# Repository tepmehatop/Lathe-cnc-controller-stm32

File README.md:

# Электронная гитара токарного станка на STM32

Контроллер электронного ходового винта (ELS) на плате **STM32F4DISCOVERY** (STM32F407VG).
Логика станка — прошивка **7e2** с форума chipmaker.ru (Arduino Mega), перенесённая без изменений
в расчётах: резьбы с привязкой к углу шпинделя, синхронная и асинхронная подача, конусы, шар,
делилка, автоциклы «Внутренний»/«Наружный», ускоренные ходы, РГИ, упоры с плавной остановкой.

Добавлено поверх 7e2:
- сенсорный дисплей ESP32 — 4.3" (JC4827W543), 10.1" (JC8012P4A1C) или 7" (JC1060P470, пока не проверен на железе);
- координаты от блока DRO HS800-2 или от линеек напрямую (квадратура, Sylvac, BIN6, iGaging, Digimatic);
- все настройки в одном файле, пересчёт таблиц резьб под свою механику;
- монитор входов для проверки проводки, проверка ядра на компьютере без платы.

## С чего начать

- **Прошить под Windows с нуля** — [docs/windows](docs/windows/README.md): готовая прошивка с GitHub или своя сборка
  в VS Code + PlatformIO, с картинками по шагам и примерами настроек.
- **Как работать на станке** — [руководство пользователя](docs/manual/README.md): экран, пульт, упоры и автоцикл,
  каждый режим с примером («резьба M20×1.5 длиной 80 мм — делайте так»), все сообщения и что с ними делать.
- **Что куда подключать** — [docs/wiring.html](docs/wiring.html): интерактивная схема — каждая нога Discovery,
  провод, деталь шилда и клемма модуля (откройте файл в браузере).
- **Как собрать** — [docs/assembly](docs/assembly/README.md): список покупок, заказ и пайка шилда, какой провод куда
  (схема на каждый разъём), первое включение по блокам. Макетка без шилда — [docs/README.md](docs/README.md).
- **G-код по Wi-Fi** — [docs/GCODE.md](docs/GCODE.md).

## Как выглядит

Снимки с дисплея 10.1" JC8012P4A1C во время автоциклов на стенде (STM32 + эмулятор шпинделя и DRO):
счётчик проходов показывает, сколько осталось и сколько всего — как «Циклов» на LCD2004.

| Резьба 1.50 мм, наружная — 14 из 16 проходов | Подача 0.20 мм/об, наружная — проход 2 из 3 |
|---|---|
|  |  |
| **Конус 30°, наружный, съём ⌀ 0.20** | **Шар ⌀ 20 мм — 40 заходов из 41** |
|  |  |
| **Асинхронная подача 300 мм/мин, съём на радиус** | **Резьба 1.50 мм, 2 захода** |
|  |  |

### Дисплей в работе

| Режимы: выбор, резьба, асинхрон, конус, G-код | Настройки, калибровка, линейки, ввод координат |
|---|---|
|  |  |

На 4.3" всё то же, только мельче.

## С чего начать

**[docs/index.html](docs/index.html)** — руководство со схемами: что купить, что куда прошить, какой
провод куда, сборка на макетке, стенд без станка, линейки, дисплеи, шилд.
Текстовая версия — [docs/README.md](docs/README.md).

## Быстро

```bash
# прошивка платы STM32 (mini-USB в разъём ST-Link) — один из вариантов:
pio run -e stm32f407_discovery -t upload   # без линеек: позиция по шагам моторов, как в исходной 7e2
pio run -e stm32f407_dro -t upload         # с блоком DRO HS800-2
pio run -e stm32f407_scales -t upload      # линейки напрямую к STM32 (тип — в els_config.h)
# прошивка дисплея: 4.3", 10.1" или 7" (jc1060p470 / _v2 / _v3 — DISPLAYS.md)
pio run -e jc4827w543 -t upload
pio run -e jc8012p4a1c -t upload
pio run -e jc1060p470 -t upload
```

Настройки — [`Core/els_config.h`](Core/els_config.h), выводы — [`Core/e2/e2_pins.h`](Core/e2/e2_pins.h).

## Выводы STM32F4DISCOVERY

Кратко по группам; полная таблица со штырьками разъёмов P1/P2 — [docs/wiring/pins.md](docs/wiring/pins.md),
карта разъёмов — [docs/wiring/discovery_pinout.svg](docs/wiring/discovery_pinout.svg).

| Что | Выводы STM32 |
|---|---|
| Энкодер шпинделя A / B | PA1 / PA8 |
| Драйвер Z (каретка): STEP / DIR / ENA | PE9 / PE10 / PE11 |
| Драйвер X (суппорт): STEP / DIR / ENA | PE13 / PE14 / PE15 |
| Тахометр, зуммер | PE8, PE12 |
| Переключатель режимов: Синхр., Асинхр., Конус <, Конус >, Резьба, Шар, Делилка, Резерв | PD0, PD1, PD2, PD3, PD6, PD7, PD10, PD11 |
| Подрежим: Внутренний / Ручной / Наружный | PC8 / PC9 / PC11 |
| Кнопки меню: Влево, Вправо, Вверх, Вниз, Выбор | PB13, PB14, PB12, PD9, PB15 |
| Джойстик: Влево, Вправо, Вверх, Вниз, ускоренный ход | PB0, PB1, PE3, PB9, PB8 |
| Кнопки упоров: Левый, Правый, Передний, Задний | PC5, PC4, PC2, PA0 |
| Светодиоды упоров: Левый, Правый, Передний, Задний | PE6, PE5, PE4, PE2 |
| РГИ: A / B; ось Z / X; масштаб ×1 / ×10 | PE7 / PC13; PC10 / PC12; PA4 / PD8 |
| Переменник подачи (АЦП) | PC1 |
| Дисплей ESP32: TX / RX | PB10 / PB11 |
| LCD2004 (I2C): SCL / SDA | PB6 / PB7 |
| Блок DRO HS800-2 (его TX) | PA3 |
| Отладочный порт (USB-UART): TX / RX | PA9 / PA10 |
| Линейки напрямую Z: A / B / REQ | PA15 / PB3 / PC6 |
| Линейки напрямую X: A / B / REQ | PB4 / PB5 / PC7 |

Все кнопки и переключатели замыкают вывод на GND; подтяжка 1 кОм к 3V платы. Схемы по блокам —
[docs/index.html](docs/index.html#blocks).

Стенд без станка — Arduino Mega с прошивкой `Simulator/dro_simulator`: TX1 (вывод 18) → PA3, GND → GND;
для режима линеек ещё D22 → PA15, D23 → PB3, D24 → PB4, D25 → PB5, D26 ← PC6, D27 ← PC7 (через 1 кОм).
Схема — [docs/wiring/emulator.svg](docs/wiring/emulator.svg).

## Устройство проекта

| Папка | Что там |
|---|---|
| `Core/e2/orig/` | файлы прошивки 7e2 без изменений |
| `Core/e2/` | основной скетч (`e2_core.cpp`), аппаратный слой STM32 (`e2_hal`), выводы, LCD2004, протокол дисплея |
| `Core/els_config.h` | все настройки |
| `Drivers/` | блок DRO HS800-2, линейки напрямую |
| `ELS_Display/`, `ELS_Display_P4/` | прошивки дисплеев 4.3" и 10.1" |
| `Simulator/dro_simulator/` | эмулятор блока DRO и линеек на Arduino Mega |
| `hardware/shield/` | шилд под Discovery (KiCad) |
| `docs/` | руководство, схемы, аудит переноса |
| `tests/`, `tools/` | проверки и вспомогательные скрипты |

## Проверки

```bash
bash tools/run_e2_sim.sh        # ядро 7e2 + аппаратный слой на компьютере: резьбы, подачи, циклы
bash tools/run_unit_tests.sh    # декодеры протоколов линеек
bash tools/build_matrix.sh      # сборка во всех вариантах настроек
```

Что перенесено и как проверено — [docs/PORT_AUDIT.md](docs/PORT_AUDIT.md); полная сверка с оригиналом по пунктам — [docs/CHECKLIST_7e2.md](docs/CHECKLIST_7e2.md).
История работ — [history.md](history.md), задачи — [BACKLOG.md](BACKLOG.md).

## Лицензия

Открытый проект. Условия лицензирования уточняются.

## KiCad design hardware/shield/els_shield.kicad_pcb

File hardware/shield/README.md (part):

# Шилд ELS под STM32F4DISCOVERY

**Rev 2 — компактный, как Shield3.0 под Mega.** Плата 96×126 мм. Discovery вставляется сверху в гнёзда лицом
вверх (USB ST-LINK — к верхнему краю): кнопки, светодиоды и оба USB остаются видны и доступны. Мелочь — SMD 0805
и SOT-23 — под Discovery (зазор ≈ 8 мм), разъёмы — штыревые 2.54 мм с защёлкой (KF2510 / Molex KK-254) по всем
четырём краям (сверху — сброс и резервные), переключатель режимов — коробка IDC 2×5 (подписи M1…M8, как на экране). На шелкографии у мелочи — номинал
(«1k», «10k», «3904»), у разъёмов — назначение каждого вывода. Схемотехника — как у шилда автора 7e2, с поправками
на 3.3-вольтовый STM32 (см. `design.py`).

## Состояние

| Что | Готово |
|---|---|
| Схема KiCad (`els_shield.kicad_sch`, PDF — `els_shield_schematic.pdf`) | да, ERC — 0 ошибок |
| Список деталей (`bom.md`, `bom.csv`) | да |
| Плата: 96×126 мм, размещение, земля с двух сторон, подписи | да |
| Дорожки | да — KiCad MCP (`autoroute`, Freerouting 2.1.0, GND тоже дорожками), полигоны земли + переходы |
| Проверка | DRC — **0 нарушений, 0 неразведённых**; сверка со схемой — цепи 1:1; поштырьково — [CHECK.md](CHECK.md), 0 замечаний |
| Gerber-файлы для заказа | `els_shield_gerbers.zip` (медь, маска, шелкография с двух сторон, контур, сверловка) |

Перед заказом обязательно:
1. Сверить расстояние между гнёздами J1/J2 с вашей платой Discovery (по чертежу UM1472 — 53.34 мм между
   крайними рядами), лучше всего — распечатать слой F.Cu в масштабе 1:1 и приложить плату.
2. Проверить снизу Discovery: под ней на шилде — SMD-детали высотой до 1.5 мм (C8 1206 — до 1.8 мм).

## Как собрать и развести

Всё генерируется из `design.py` — единого описания деталей и цепей. Цепи выводов STM32 берутся из
`Core/e2/e2_pins.h`, поэтому шилд всегда совпадает с прошивкой.

1. Схема, BOM, размещение (KiCad 10, macOS: `/Applications/KiCad`): `bash hardware/shield/build.sh`.
2. Трассировка — KiCad MCP: `open_project` → `autoroute` (Freerouting 2.1.0 под Java 21; 3–5 попыток, берётся
   лучшая; если какая-то цепь осталась — `autoroute` ещё раз поверх, он доведёт только недостающее).
3. `$KPY hardware/shield/fix_zones.py` — полигоны земли с двух сторон, связность земли, дубликаты и хвосты
   дорожек, заливка (`$KPY` — Python KiCad: `/Applications/KiCad/KiCad.app/Contents/Frameworks/Python.framework/Versions/Current/bin/python3`).
4. MCP `add_gnd_stitching_vias` (сетка 6 мм) → `save_board` → `fix_zones.py` ещё раз (переходы с малым зазором
   и на выводах разъёмов — прочь).
5. `$KPY hardware/shield/widen_power.py` — дорожки +5V до 1.0 мм там, где позволяет DRC.
   Затем `$KPY hardware/shield/fix_holes.py` — у крепёжных отверстий только земля (ручная перекладка трёх дорожек,
   см. «Что проверено»); после новой трассировки координаты в нём нужно сверить заново.
6. Проверка: MCP `run_drc` (и со сверкой схемы), `$KPY hardware/shield/verify.py` → CHECK.md; файлы —
   MCP `export_gerbers` + `export_drill` в `gerbers/`, архив `els_shield_gerbers.zip`.

Размещение генерируется заново из `design.py` — после него трассировку нужно повторить.

**Разъёмы верхнего края (J24–J27) добавлены 2026-11-12 в уже разведённую плату, старая разводка не менялась:**
`$KPY add_reserve.py` (детали и подписи из `design.py`) → `$KPY route_reserve.py prep <снимок платы до добавления>`
(старые дорожки закреплены, полигоны сняты, `build/res2.dsn`) → Freerouting 2.1
(`java -jar freerouting.jar -de build/res2.dsn -do build/res2.ses -mp 100 -mt 1`) → `$KPY merge_ses.py build/res2.ses`
(в плату — только новые дорожки, без земли) → `$KPY fix_reserve.py`, `route_grid.py` + `add_path.py` (что Freerouting
не довёл), `$KPY fix_reserve2.py`, `$KPY fix_silk_top.py`. Новые цепи — класс Reserve (дорожка 0.2 мм, переход 0.6/0.3).
При полной перегенерации платы из `design.py` эти шаги нужно повторить заново.

## Что проверено и что знать при сборке

Резервные разъёмы (2026-11-12): исходные 1425 дорожек и переходов на месте (сверка по геометрии со снимком до
добавления), ни одна старая деталь не сдвинута, у старых площадок цепь появилась только у 6 ранее пустых выводов J1;
новые цепи прослежены от площадки до площадки; DRC — 0 нарушений, 0 неразведённых; ERC — 0; сверка со схемой — без
цепи только неиспользуемые выводы Discovery; CHECK.md — 0 замечаний. PD12 и PD14 не выведены: внутренний ряд P1, путь
к ним — около 150 мм с 9–10 переходами через плотную середину платы.

Проверено вручную перед заказом (2026-11-12), по первоисточникам — не по отчётам скриптов:
- Гнёзда J1/J2 — по рис. 10 UM1472: все 100 выводов P1/P2 по именам, 53.34 мм между крайними рядами, ряды выровнены,
  нечётные выводы — левый столбец, Discovery лицом вверх без зеркаления.
- Каждый вывод гнёзд → цепь → функция прошивки (e2_pins.h) и логика входов — по коду автора 7e2 (Menu.ino: шаблоны
  Mode/Submode/Joy/Buttons/Limit/Hand) и схеме ELS_V7: совпадает, включая порядок M1…M8 и подрежимов (у автора на
  схеме A13/A15 подписаны наоборот — верно по коду).
- Каждая деталь: номинал, корпус, обе площадки и куда они идут (33 подтяжки, 7 ключей с 1k/10k, 4 × 220, 100, 6 × 470,
  C1–C8, D1 — катод к Discovery). Цоколёвка MMBT3904 SOT-23: 1 Б, 2 Э, 3 К.
- Медь каждой цепи — путь от площадки до каждой другой площадки по дорожкам и переходам: все 87 цепей замкнуты,
  земля — все 50 площадок даже без полигонов. Шелкография — каждая из 87 подписей против своей площадки и цепи.
- Ключ вилки J7 — к краю платы, со стороны ряда 1-3-5-7-9; жила шлейфа N = вывод N = режим M N.
- Механика: разъёмы и вилка J7 не попадают под Discovery (она занимает x 15…81, y 11…108 мм).
- Найдено и исправлено: у отверстия H3 дорожка и переход DRO_RX были в 2.4 мм от центра (под головкой винта —
  металлическая стойка могла замкнуть линию на корпус), у H2 — LED_LEFT_K/LED_RIGHT_K в 3.3–3.9 мм (под шайбой).
  Переложены (fix_holes.py): ближайшая сигнальная медь теперь в 4.8 мм и дальше; рядом с отверстиями — только земля.

Проверено ранее (2026-11-08):
- Каждый контакт каждого разъёма: подпись на плате → медь → деталь → гнездо Discovery → вывод STM32 → функция
  прошивки ([CHECK.md](CHECK.md), из разведённой платы). Все выводы прошивки выведены, лишних нет.
- Таблица гнёзд P1/P2 — по UM1472 (табл. 5): все 81 сигнальный вывод совпадают; геометрия — по рис. 10:
  53.34 мм между крайними рядами, вывод 1 — сверху слева, нечётные — левый столбец.
- Что висит на выводах на самой Discovery (UM1472, схемы): PA4, PC7, PC10, PC12, PB6 — аудио-ЦАП (держится в
  сбросе, PD4 = 0); PC4 — к микрофону через R49, **не установлен**; PE3 — выбор акселерометра (PA5–PA7 не
  используются); PB9 — подтяжка 4.7 кОм; PA0 — кнопка USER. Мешающих нет.

Знать:
- **Питание.** Блок 5 В — на J3 «ПИТАНИЕ 5В», от 2 А (с дисплеем 10.1" — 3 А). Discovery питается от него через
  диод D1: USB ST-LINK без блока питания питает только Discovery, но не дисплей и не остальное (выводы 5V/3V
  Discovery — не больше 100 мА наружу, UM1472 п. 4.3). +3V шилда — от Discovery: подтяжки и светодиоды — до 60 мА.
- **Светодиоды упоров** — красные, жёлтые или зелёные (от 3.3 В через 220 Ом). Синие и белые светить не будут.
- **Драйверы моторов** — «+» входов на +5 В (контакты PUL+/DIR+/ENA+), «−» — на ключи. В прошивке
  `DRIVER_SIGNALS_DIRECT 0` (по умолчанию).
- **Блок DRO** — выход TTL (как у автора 7e2). Если у блока RS-232 (±12 В) — нужен преобразователь (MAX3232).
- **LCD2004 по I2C** — у модуля свои подтяжки к 5 В; работает, но лучше снять их с модуля (на Discovery есть
  свои к 3 В).
- **Отладочный порт J21:** TX (PA9) на Discovery соединён с VBUS micro-USB и конденсатором 4.7 мкФ (C49) —
  передача от STM32 на 115200 не работает, приём (PA10) работает. Для работы станка порт не нужен.
- **Пайка земли:** выводы GND разъёмов подключены к полигонам сплошь — паяльник от 40 Вт.

## Что на плате

Схемы подключения каждого разъёма (провод → клемма модуля), список покупок и порядок пайки —
[docs/assembly](../../docs/assembly/README.md).

| Разъём | Что подключать |
|---|---|
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
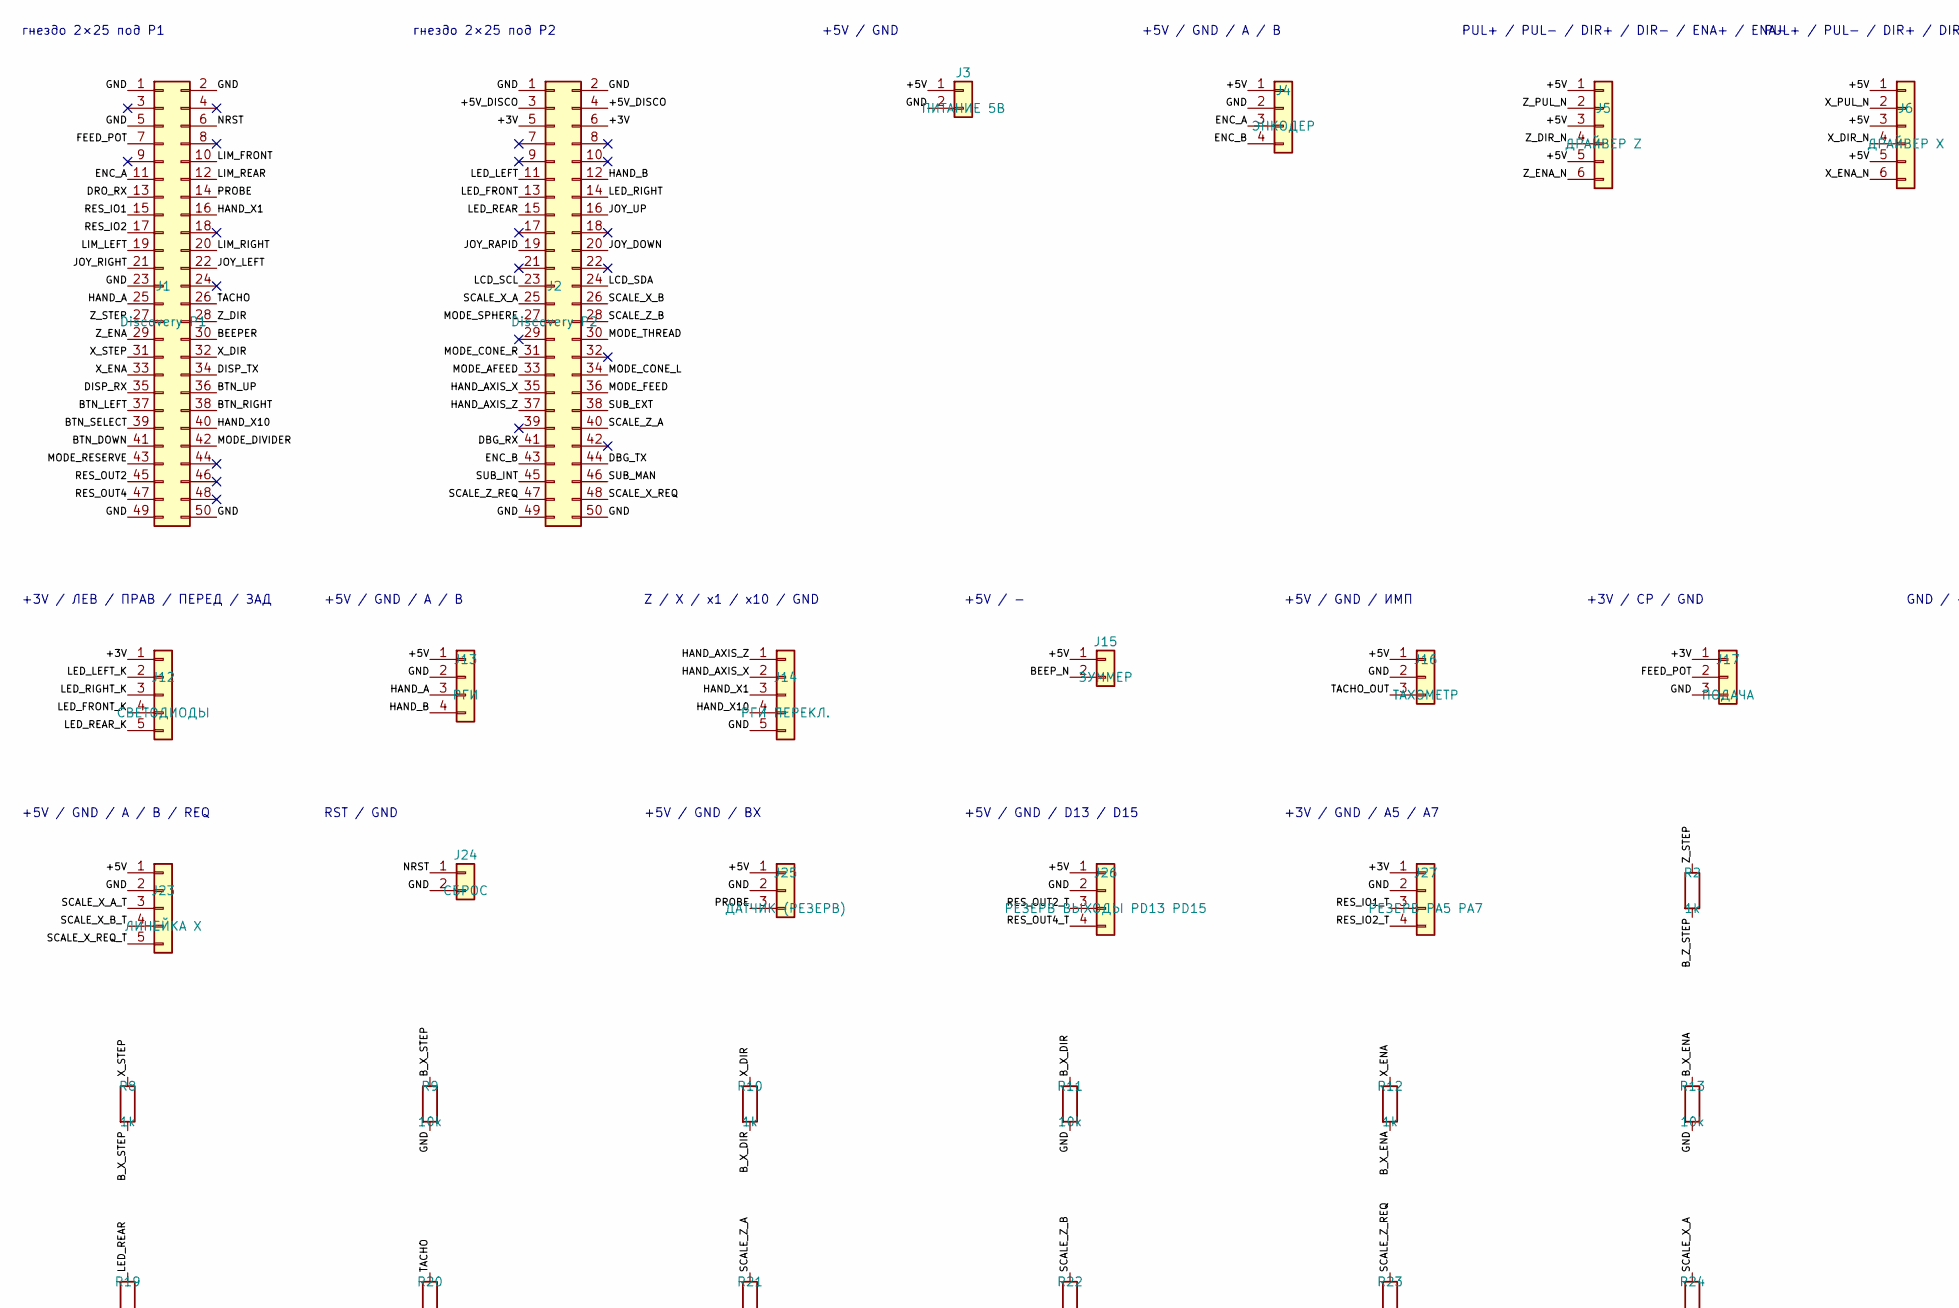
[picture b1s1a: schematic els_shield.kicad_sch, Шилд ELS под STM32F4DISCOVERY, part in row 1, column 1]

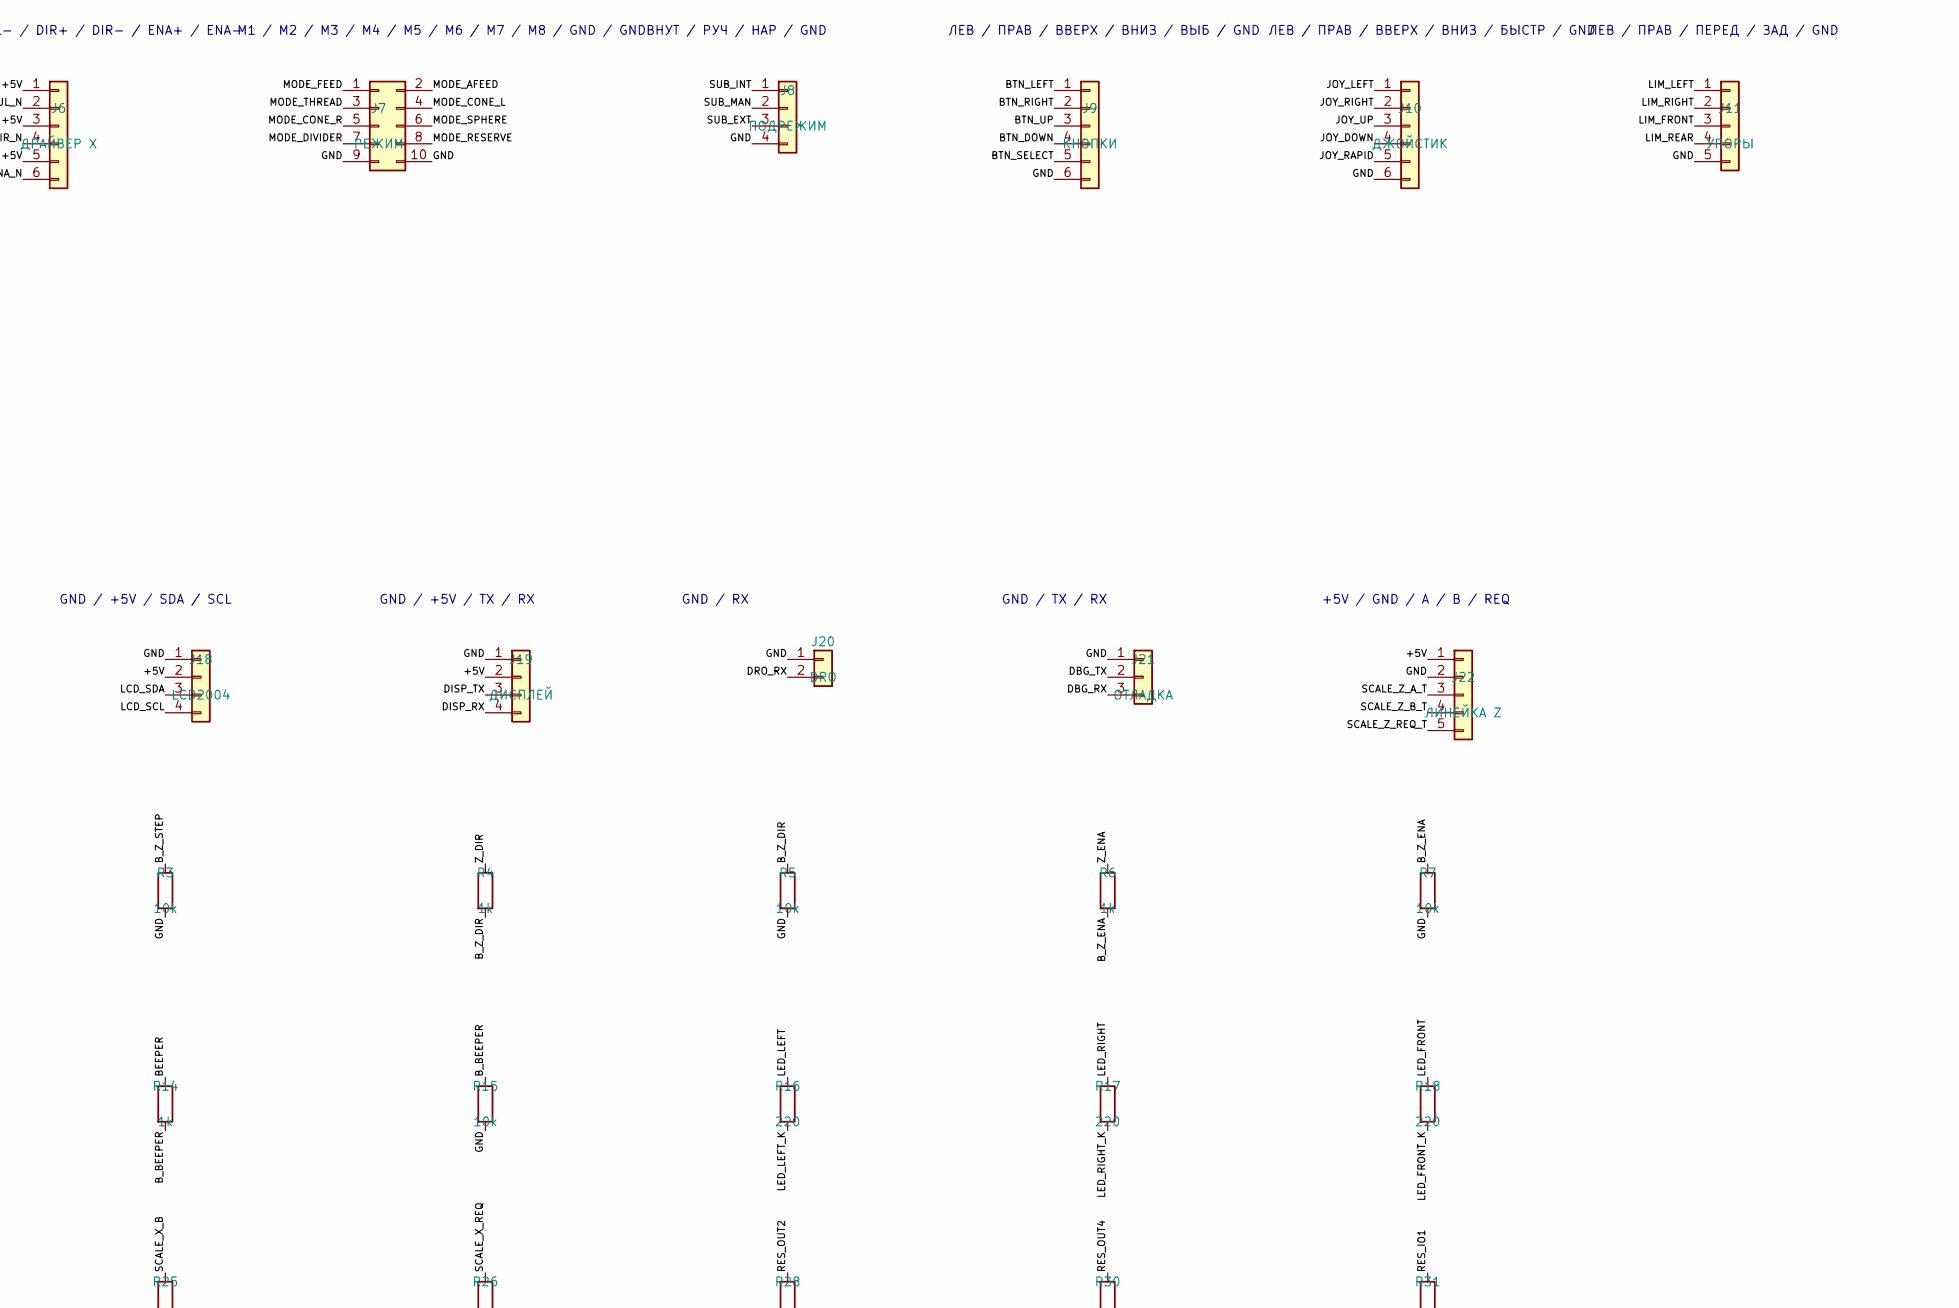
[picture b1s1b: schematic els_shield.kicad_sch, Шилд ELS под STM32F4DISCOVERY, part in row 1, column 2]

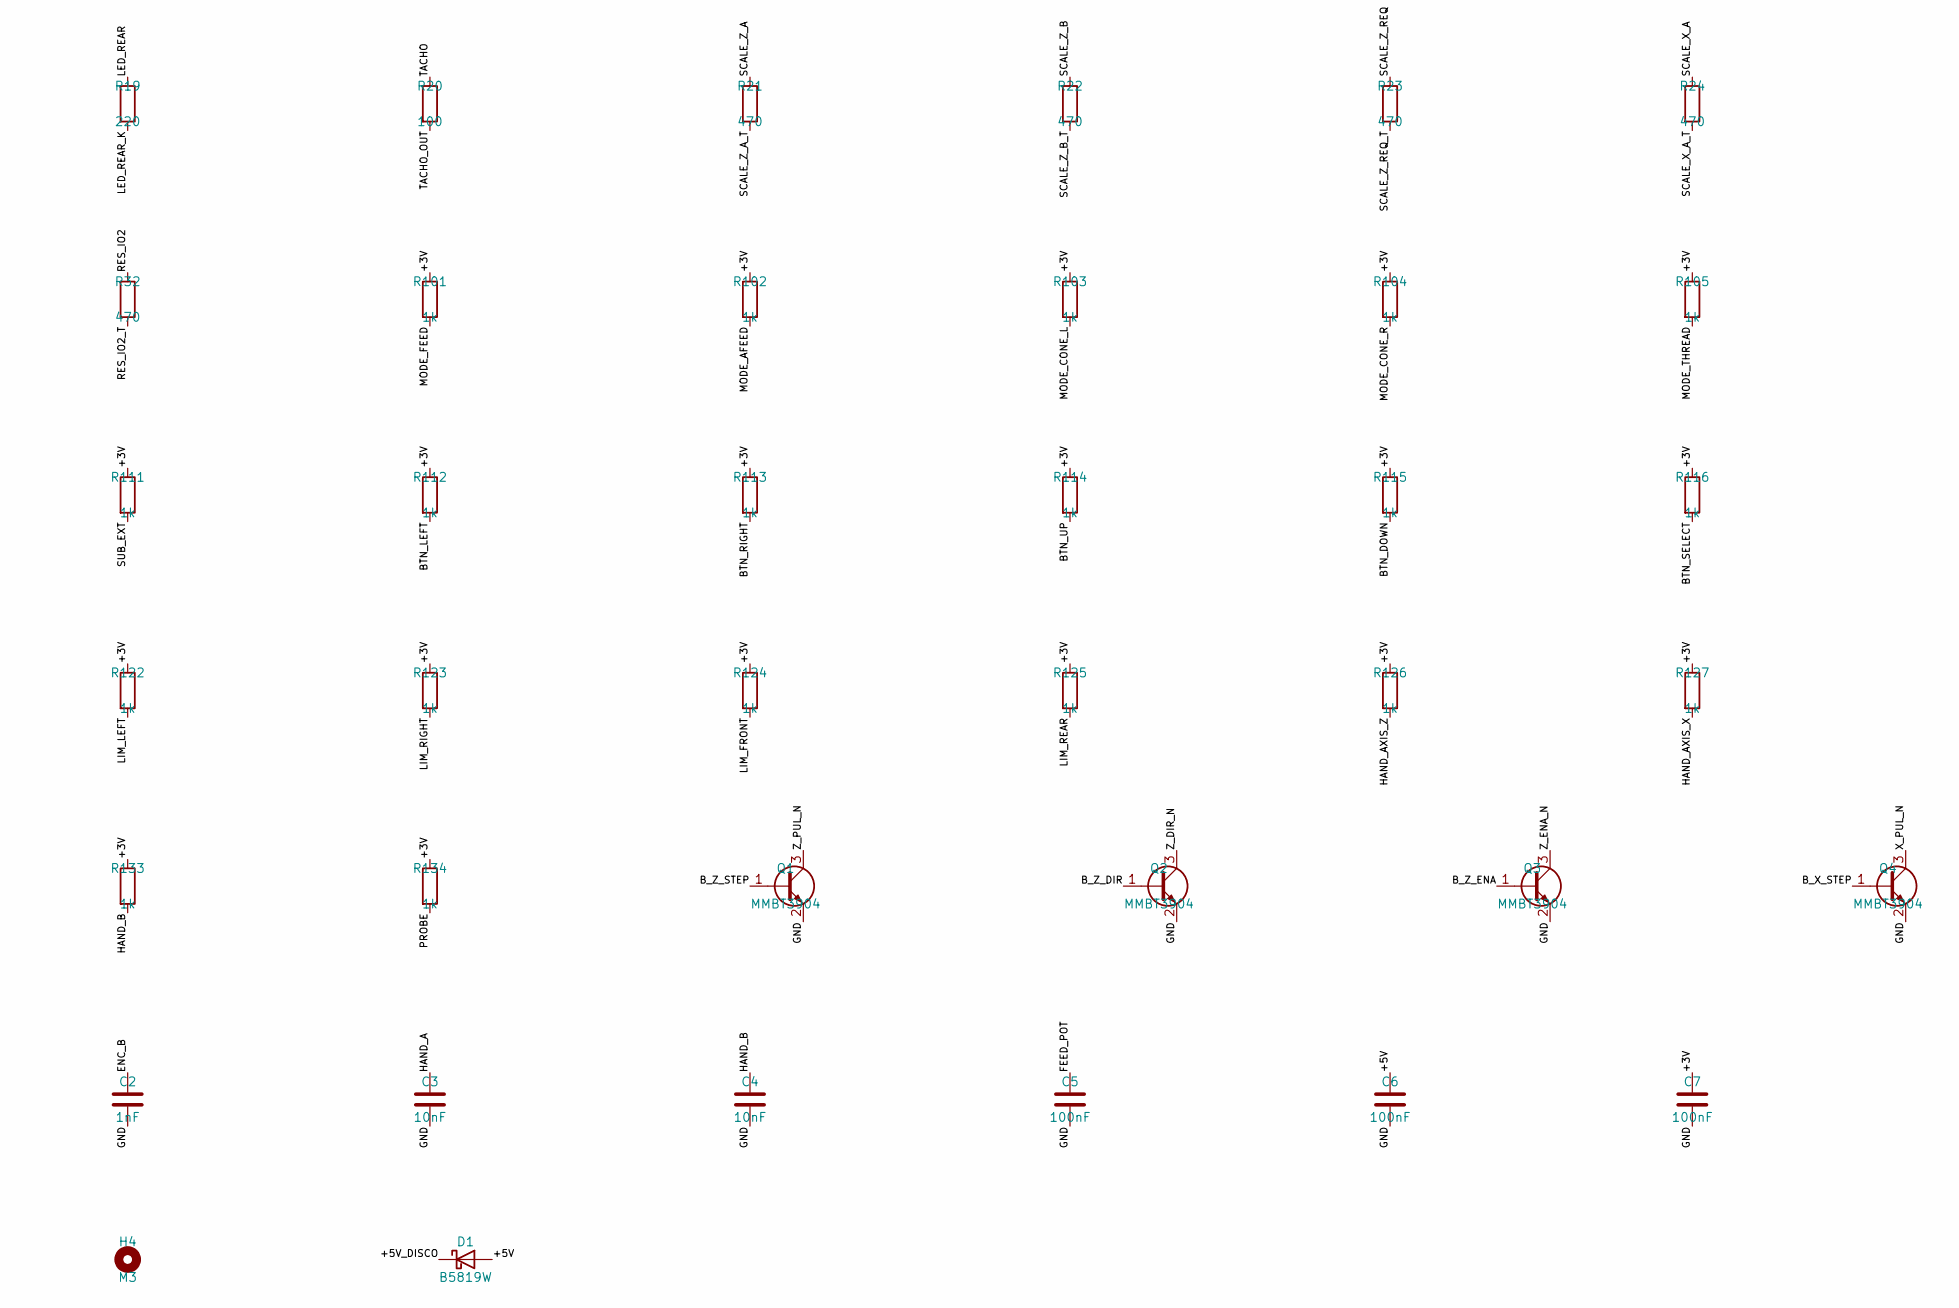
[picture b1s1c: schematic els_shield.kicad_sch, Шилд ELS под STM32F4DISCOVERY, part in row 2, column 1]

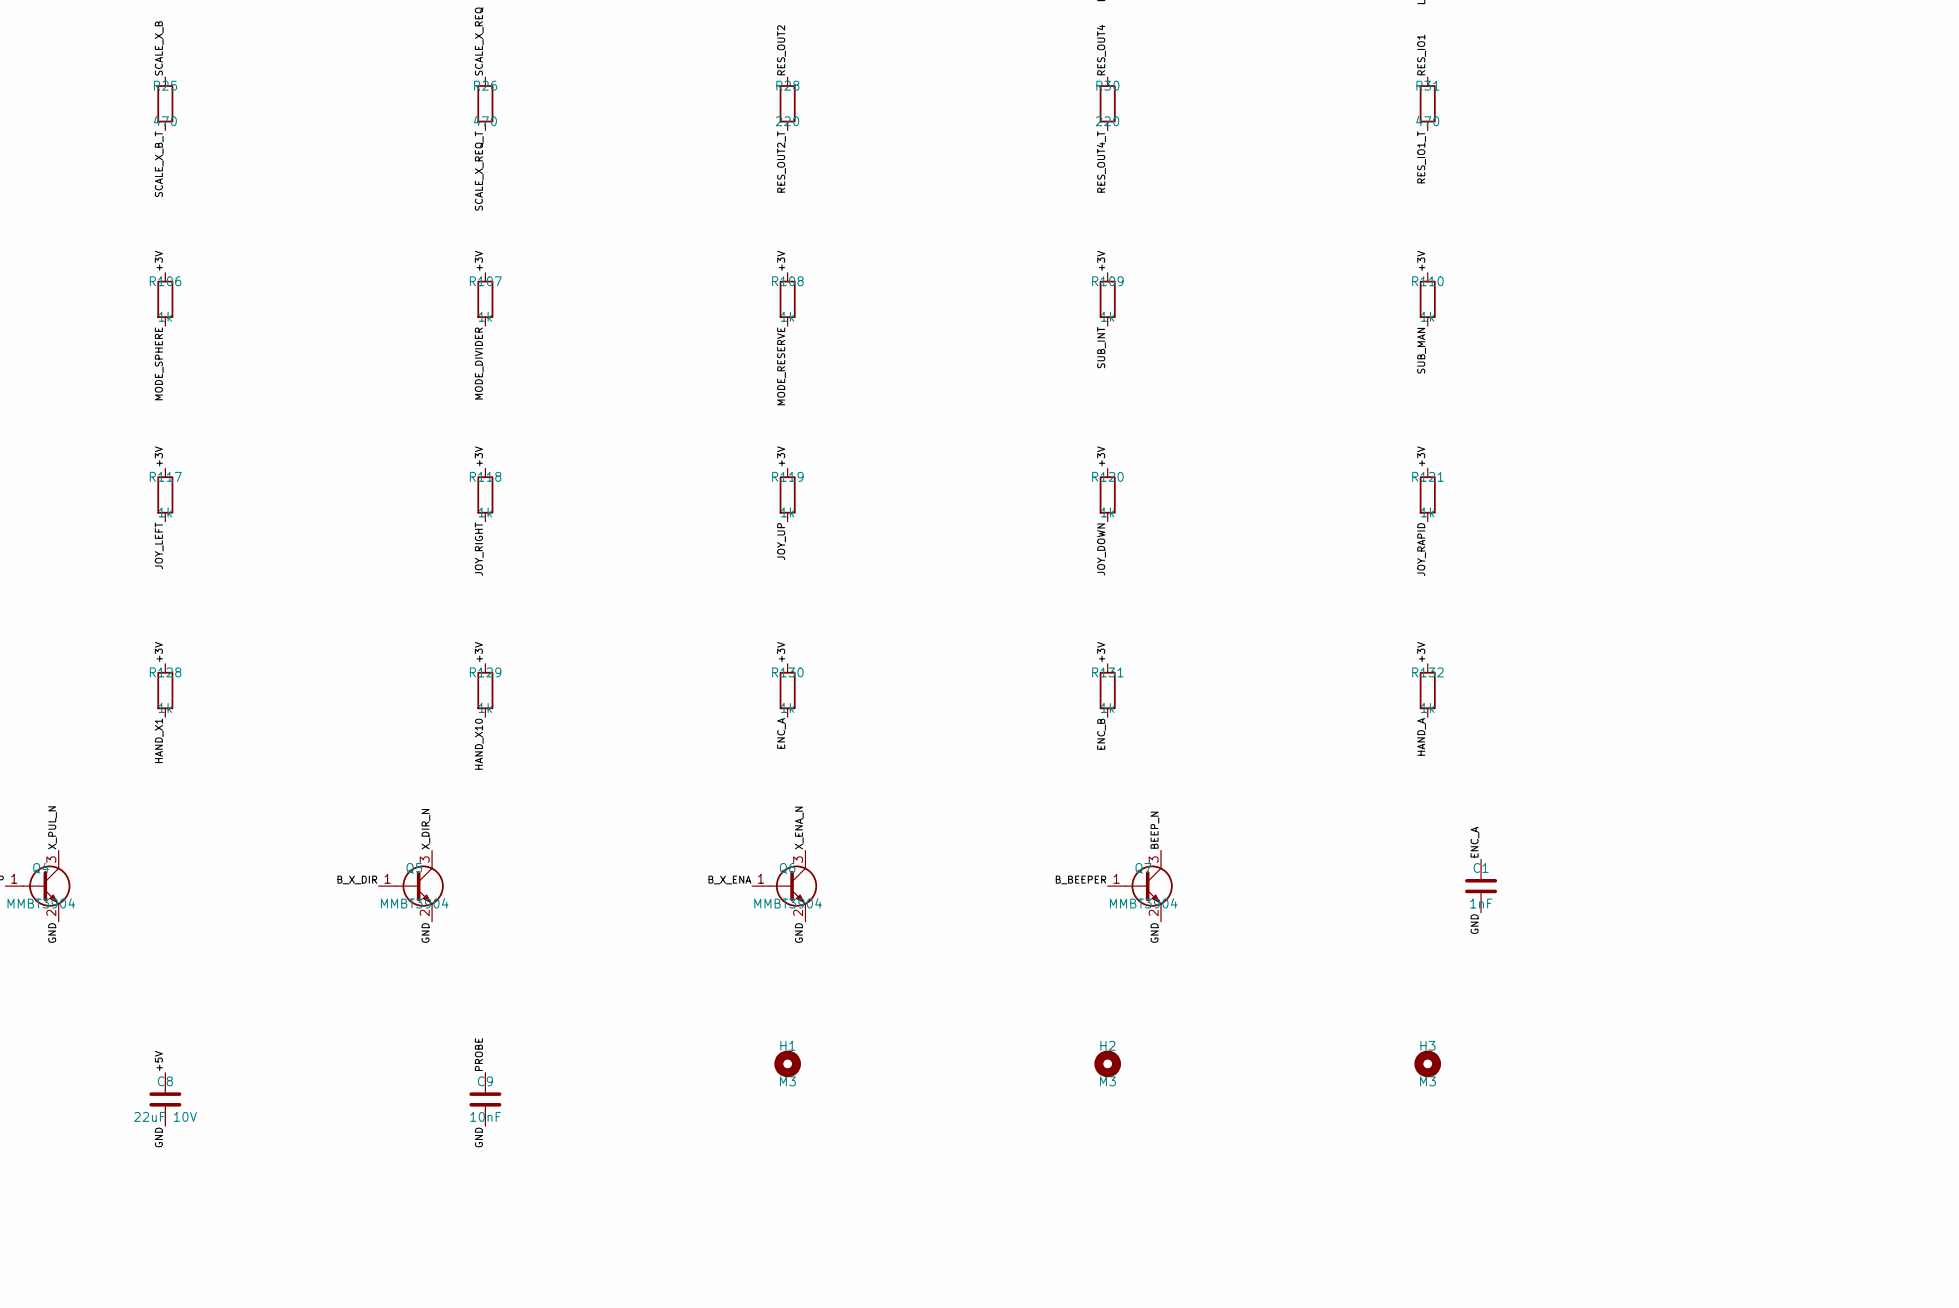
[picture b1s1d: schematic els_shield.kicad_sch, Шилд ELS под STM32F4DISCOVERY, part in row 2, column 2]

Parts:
C1, C2: 1nF; C_0805_2012Metric
C3, C4, C9: 10nF; C_0805_2012Metric
C5, C6, C7: 100nF; C_0805_2012Metric
C8: 22uF 10V; C_1206_3216Metric
D1: B5819W; D_SOD-123
H1, H2, H3, H4: M3; MountingHole_3.2mm_M3
J1: Discovery P1; PinHeader_2x25_P2.54mm_Vertical
J2: Discovery P2; PinHeader_2x25_P2.54mm_Vertical
J3: ПИТАНИЕ 5В; Molex_KK-254_AE-6410-02A_1x02_P2.54mm_Vertical
J4: ЭНКОДЕР; Molex_KK-254_AE-6410-04A_1x04_P2.54mm_Vertical
J5: ДРАЙВЕР Z; Molex_KK-254_AE-6410-06A_1x06_P2.54mm_Vertical
J6: ДРАЙВЕР X; Molex_KK-254_AE-6410-06A_1x06_P2.54mm_Vertical
J7: РЕЖИМ; IDC-Header_2x05_P2.54mm_Vertical
J8: ПОДРЕЖИМ; Molex_KK-254_AE-6410-04A_1x04_P2.54mm_Vertical
J9: КНОПКИ; Molex_KK-254_AE-6410-06A_1x06_P2.54mm_Vertical
J10: ДЖОЙСТИК; Molex_KK-254_AE-6410-06A_1x06_P2.54mm_Vertical
J11: УПОРЫ; Molex_KK-254_AE-6410-05A_1x05_P2.54mm_Vertical
J12: СВЕТОДИОДЫ; Molex_KK-254_AE-6410-05A_1x05_P2.54mm_Vertical
J13: РГИ; Molex_KK-254_AE-6410-04A_1x04_P2.54mm_Vertical
J14: РГИ ПЕРЕКЛ.; Molex_KK-254_AE-6410-05A_1x05_P2.54mm_Vertical
J15: ЗУММЕР; Molex_KK-254_AE-6410-02A_1x02_P2.54mm_Vertical
J16: ТАХОМЕТР; Molex_KK-254_AE-6410-03A_1x03_P2.54mm_Vertical
J17: ПОДАЧА; Molex_KK-254_AE-6410-03A_1x03_P2.54mm_Vertical
J18: LCD2004; Molex_KK-254_AE-6410-04A_1x04_P2.54mm_Vertical
J19: ДИСПЛЕЙ; Molex_KK-254_AE-6410-04A_1x04_P2.54mm_Vertical
J20: DRO; Molex_KK-254_AE-6410-02A_1x02_P2.54mm_Vertical
J21: ОТЛАДКА; Molex_KK-254_AE-6410-03A_1x03_P2.54mm_Vertical
J22: ЛИНЕЙКА Z; Molex_KK-254_AE-6410-05A_1x05_P2.54mm_Vertical
J23: ЛИНЕЙКА X; Molex_KK-254_AE-6410-05A_1x05_P2.54mm_Vertical
J24: СБРОС; Molex_KK-254_AE-6410-02A_1x02_P2.54mm_Vertical
J25: ДАТЧИК (РЕЗЕРВ); Molex_KK-254_AE-6410-03A_1x03_P2.54mm_Vertical
J26: РЕЗЕРВ ВЫХОДЫ PD13 PD15; Molex_KK-254_AE-6410-04A_1x04_P2.54mm_Vertical
J27: РЕЗЕРВ PA5 PA7; Molex_KK-254_AE-6410-04A_1x04_P2.54mm_Vertical
Q1, Q2, Q3, Q4, Q5, Q6, Q7: MMBT3904; SOT-23
R2, R4, R6, R8, R10, R12, R14, R101, R102, R103, R104, R105, R106, R107, R108, R109, R110, R111, R112, R113, R114, R115, R116, R117, R118, R119, R120, R121, R122, R123, R124, R125, R126, R127, R128, R129, R130, R131, R132, R133, R134: 1k; R_0805_2012Metric
R3, R5, R7, R9, R11, R13, R15: 10k; R_0805_2012Metric
R16, R17, R18, R19, R28, R30: 220; R_0805_2012Metric
R20: 100; R_0805_2012Metric
R21, R22, R23, R24, R25, R26, R31, R32: 470; R_0805_2012Metric

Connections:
+3V: C7.1, J2.5, J2.6, J12.1, J17.1, J27.1, R101.1, R102.1, R103.1, R104.1, R105.1, R106.1, R107.1, R108.1, R109.1, R110.1, R111.1, R112.1, R113.1, R114.1, R115.1, R116.1, R117.1, R118.1, R119.1, R120.1, R121.1, R122.1, R123.1, R124.1, R125.1, R126.1, R127.1, R128.1, R129.1, R130.1, R131.1, R132.1, R133.1, R134.1
+5V: C6.1, C8.1, D1.2 (A), J3.1, J4.1, J5.1, J5.3, J5.5, J6.1, J6.3, J6.5, J13.1, J15.1, J16.1, J18.2, J19.2, J22.1, J23.1, J25.1, J26.1
+5V_DISCO: D1.1 (K), J2.3, J2.4
BEEPER: J1.30, R14.1
BEEP_N: J15.2, Q7.3 (C)
BTN_DOWN: J1.41, J9.4, R115.2
BTN_LEFT: J1.37, J9.1, R112.2
BTN_RIGHT: J1.38, J9.2, R113.2
BTN_SELECT: J1.39, J9.5, R116.2
BTN_UP: J1.36, J9.3, R114.2
B_BEEPER: Q7.1 (B), R14.2, R15.1
B_X_DIR: Q5.1 (B), R10.2, R11.1
B_X_ENA: Q6.1 (B), R12.2, R13.1
B_X_STEP: Q4.1 (B), R8.2, R9.1
B_Z_DIR: Q2.1 (B), R4.2, R5.1
B_Z_ENA: Q3.1 (B), R6.2, R7.1
B_Z_STEP: Q1.1 (B), R2.2, R3.1
DBG_RX: J2.41, J21.3
DBG_TX: J2.44, J21.2
DISP_RX: J1.35, J19.4
DISP_TX: J1.34, J19.3
DRO_RX: J1.13, J20.2
ENC_A: C1.1, J1.11, J4.3, R130.2
ENC_B: C2.1, J2.43, J4.4, R131.2
FEED_POT: C5.1, J1.7, J17.2
GND: C1.2, C2.2, C3.2, C4.2, C5.2, C6.2, C7.2, C8.2, C9.2, J1.1, J1.2, J1.5, J1.23, J1.49, J1.50, J2.1, J2.2, J2.49, J2.50, J3.2, J4.2, J7.9, J7.10, J8.4, J9.6, J10.6, J11.5, J13.2, J14.5, J16.2, J17.3, J18.1, J19.1, J20.1, J21.1, J22.2, J23.2, J24.2, J25.2, J26.2, J27.2, Q1.2 (E), Q2.2 (E), Q3.2 (E), Q4.2 (E), Q5.2 (E), Q6.2 (E), Q7.2 (E), R3.2, R5.2, R7.2, R9.2, R11.2, R13.2, R15.2
HAND_A: C3.1, J1.25, J13.3, R132.2
HAND_AXIS_X: J2.35, J14.2, R127.2
HAND_AXIS_Z: J2.37, J14.1, R126.2
HAND_B: C4.1, J2.12, J13.4, R133.2
HAND_X1: J1.16, J14.3, R128.2
HAND_X10: J1.40, J14.4, R129.2
JOY_DOWN: J2.20, J10.4, R120.2
JOY_LEFT: J1.22, J10.1, R117.2
JOY_RAPID: J2.19, J10.5, R121.2
JOY_RIGHT: J1.21, J10.2, R118.2
JOY_UP: J2.16, J10.3, R119.2
LCD_SCL: J2.23, J18.4
LCD_SDA: J2.24, J18.3
LED_FRONT: J2.13, R18.1
LED_FRONT_K: J12.4, R18.2
LED_LEFT: J2.11, R16.1
LED_LEFT_K: J12.2, R16.2
LED_REAR: J2.15, R19.1
LED_REAR_K: J12.5, R19.2
LED_RIGHT: J2.14, R17.1
LED_RIGHT_K: J12.3, R17.2
LIM_FRONT: J1.10, J11.3, R124.2
LIM_LEFT: J1.19, J11.1, R122.2
LIM_REAR: J1.12, J11.4, R125.2
LIM_RIGHT: J1.20, J11.2, R123.2
MODE_AFEED: J2.33, J7.2, R102.2
MODE_CONE_L: J2.34, J7.4, R103.2
MODE_CONE_R: J2.31, J7.5, R104.2
MODE_DIVIDER: J1.42, J7.7, R107.2
MODE_FEED: J2.36, J7.1, R101.2
MODE_RESERVE: J1.43, J7.8, R108.2
MODE_SPHERE: J2.27, J7.6, R106.2
MODE_THREAD: J2.30, J7.3, R105.2
NRST: J1.6, J24.1
PROBE: C9.1, J1.14, J25.3, R134.2
RES_IO1: J1.15, R31.1
RES_IO1_T: J27.3, R31.2
RES_IO2: J1.17, R32.1
RES_IO2_T: J27.4, R32.2
RES_OUT2: J1.45, R28.1
RES_OUT2_T: J26.3, R28.2
RES_OUT4: J1.47, R30.1
RES_OUT4_T: J26.4, R30.2
SCALE_X_A: J2.25, R24.1
SCALE_X_A_T: J23.3, R24.2
SCALE_X_B: J2.26, R25.1
SCALE_X_B_T: J23.4, R25.2
SCALE_X_REQ: J2.48, R26.1
SCALE_X_REQ_T: J23.5, R26.2
SCALE_Z_A: J2.40, R21.1
SCALE_Z_A_T: J22.3, R21.2
SCALE_Z_B: J2.28, R22.1
SCALE_Z_B_T: J22.4, R22.2
SCALE_Z_REQ: J2.47, R23.1
SCALE_Z_REQ_T: J22.5, R23.2
SUB_EXT: J2.38, J8.3, R111.2
SUB_INT: J2.45, J8.1, R109.2
SUB_MAN: J2.46, J8.2, R110.2
TACHO: J1.26, R20.1
TACHO_OUT: J16.3, R20.2
X_DIR: J1.32, R10.1
X_DIR_N: J6.4, Q5.3 (C)
X_ENA: J1.33, R12.1
X_ENA_N: J6.6, Q6.3 (C)
X_PUL_N: J6.2, Q4.3 (C)
X_STEP: J1.31, R8.1
Z_DIR: J1.28, R4.1
Z_DIR_N: J5.4, Q2.3 (C)
Z_ENA: J1.29, R6.1
Z_ENA_N: J5.6, Q3.3 (C)
Z_PUL_N: J5.2, Q1.3 (C)
Z_STEP: J1.27, R2.1

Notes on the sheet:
гнездо 2×25 под P1
гнездо 2×25 под P2
+5V / GND
+5V / GND / A / B
PUL+ / PUL- / DIR+ / DIR- / ENA+ / ENA-
M1 / M2 / M3 / M4 / M5 / M6 / M7 / M8 / GND / GND
ВНУТ / РУЧ / НАР / GND
ЛЕВ / ПРАВ / ВВЕРХ / ВНИЗ / ВЫБ / GND
ЛЕВ / ПРАВ / ВВЕРХ / ВНИЗ / БЫСТР / GND
ЛЕВ / ПРАВ / ПЕРЕД / ЗАД / GND
+3V / ЛЕВ / ПРАВ / ПЕРЕД / ЗАД
Z / X / x1 / x10 / GND
+5V / -
+5V / GND / ИМП
+3V / СР / GND
GND / +5V / SDA / SCL
GND / +5V / TX / RX
GND / RX
GND / TX / RX
+5V / GND / A / B / REQ
RST / GND
+5V / GND / ВХ
+5V / GND / D13 / D15
+3V / GND / A5 / A7

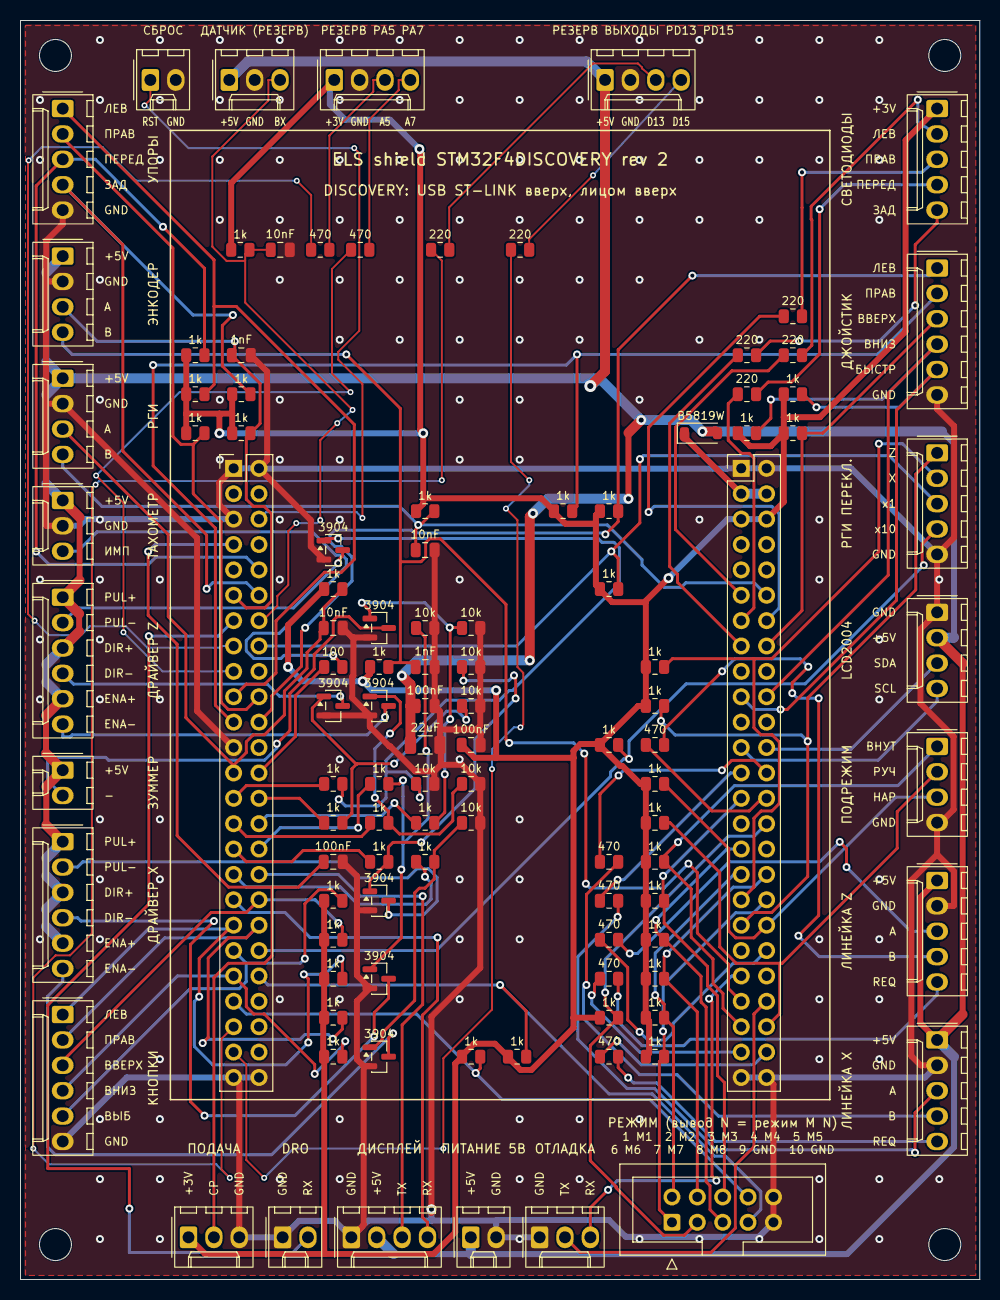
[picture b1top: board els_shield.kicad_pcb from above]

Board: 2 copper layers, 96.0 x 126.0 mm, 111 parts (0 on the bottom side), 98 nets.

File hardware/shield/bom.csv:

Количество,Деталь,Номинал,Позиции
4,"Вилка 2 конт., шаг 2.54 мм, прямая, с защёлкой (KF2510-2P / Molex KK-254) + ответная часть",,J3 J15 J20 J24
4,"Вилка 3 конт., шаг 2.54 мм, прямая, с защёлкой (KF2510-3P / Molex KK-254) + ответная часть",,J16 J17 J21 J25
7,"Вилка 4 конт., шаг 2.54 мм, прямая, с защёлкой (KF2510-4P / Molex KK-254) + ответная часть",,J4 J8 J13 J18 J19 J26 J27
5,"Вилка 5 конт., шаг 2.54 мм, прямая, с защёлкой (KF2510-5P / Molex KK-254) + ответная часть",,J11 J12 J14 J22 J23
4,"Вилка 6 конт., шаг 2.54 мм, прямая, с защёлкой (KF2510-6P / Molex KK-254) + ответная часть",,J5 J6 J9 J10
1,"Вилка IDC 2×5 в корпусе (box header), шаг 2.54 мм, прямая",,J7
1,"Гнездо (female) 2×25, шаг 2.54 мм, прямое — под Discovery",Discovery P1,J1
1,"Гнездо (female) 2×25, шаг 2.54 мм, прямое — под Discovery",Discovery P2,J2
1,"Диод Шоттки SOD-123, 1 А 40 В (B5819W или 1N5819W); полоска на корпусе — катод",B5819W,D1
3,"Конденсатор керамический SMD 0805, X7R, 16 В и выше",100nF,C5 C6 C7
3,"Конденсатор керамический SMD 0805, X7R, 16 В и выше",10nF,C3 C4 C9
2,"Конденсатор керамический SMD 0805, X7R, 16 В и выше",1nF,C1 C2
1,"Конденсатор керамический SMD 1206, X5R",22uF 10V,C8
1,"Резистор SMD 0805, 5 %",100,R20
7,"Резистор SMD 0805, 5 %",10k,R3 R5 R7 R9 R11 R13 R15
41,"Резистор SMD 0805, 5 %",1k,R101 R102 R103 R104 R105 R106 R107 R108 R109 R110 R111 R112 R113 R114 R115 R116 R117 R118 R119 R120 R121 R122 R123 R124 R125 R126 R127 R128 R129 R130 R131 R132 R133 R2 R4 R6 R8 R10 R12 R14 R134
6,"Резистор SMD 0805, 5 %",220,R16 R17 R18 R19 R28 R30
8,"Резистор SMD 0805, 5 %",470,R21 R22 R23 R24 R25 R26 R31 R32
7,"Транзистор NPN SMD SOT-23 (MMBT3904, маркировка 1A; аналог MMBT2222A)",MMBT3904,Q1 Q2 Q3 Q4 Q5 Q6 Q7

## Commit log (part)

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2026-04-05 init: скелет проекта ELS на STM32F407
    - platformio.ini: окружения для STM32F4DISCOVERY и ESP32-S3 JC4827W543
    - Core/els_config.h: единый конфиг файл (все пины, флаги, параметры механики)
    - docs/pinout.html: интерактивная схема подключения (3 стиля: блок-диаграмма,
    chip view, таблица пинов с поиском и сортировкой)
    - .gitignore: build артефакты, AGREEMENTS.md (не публикуется)
    Платформа: STM32F407VGT6 @ 168МГц, STM32duino Arduino Core
2026-04-06 fix(docs): устранить наложения и добавить HiDPI рендеринг в canvas-схеме
    - devicePixelRatio: canvas.width/height умножаются на dpr, ctx.scale(dpr)
    → текст чёткий на Retina/HiDPI при любом zoom
    - Уникальные x-lane для каждого провода (объекты T/TR):
    Left: PA3=1220, PA9=1175, PA10=1140, PB6=1080, PB7=1040,
    PA0=990, PA1=950, PC2=900, PC3=860, PD0=820... и т.д.
    Right: PE0=1720, PE1=1756, PE8=1720, PE9-PE11=1720/56/92...
2026-04-06 feat(etap1): скелет проекта STM32 — компилируется
    - src/main.cpp: точка входа setup()/loop() → ELS_Init()/ELS_Loop()
    - Core/els_main.cpp/h: инициализация и главный цикл
    - Core/els_state.cpp/h: глобальное состояние станка (режимы, позиции, параметры)
    - Drivers/drv_dro.cpp/h: заглушка DRO HS800-2 (Этап 2)
    - Drivers/drv_display.cpp/h: заглушка ESP32 дисплея (Этап 3)
    - Drivers/drv_lcd2004.cpp/h: заглушка LCD2004 I2C (Этап 4)
2026-04-06 feat(etap2): драйвер DRO HS800-2 — парсер пакетов + CRC16/MODBUS
    - HardwareSerial(PA3, PA2) = USART2 RX, 57600/8N1
    - Interrupt-driven приём (HardwareSerial STM32duino) — CPU не блокируется
    - Парсер: поиск SOF(0xFE), накопление 29 байт, проверка EOF(0xEF)
    - CRC16/MODBUS: bytes[1..25], сверка с bytes[26..27]
    - Ресинхронизация при потере пакета (поиск SOF в буфере)
    - X = bytes[6..9] int32 LE, Y = bytes[10..13] int32 LE
2026-04-06 feat(etap3): драйвер ESP32 дисплея — UART8 + полный протокол
    - HardwareSerial(PE1, PE0) = UART8 RX/TX, 115200/8N1
    - TX: SendCmd/SendInt/SendInt2 → формат <CMD:val>\n
    - Все команды протокола: POS_Z/POS_X, MODE, SUBMODE, FEED, AFEED,
    RPM, OTSKOK_Z, TENSION_Z, LIMITS, ALERT, SELECTMENU, ANGLE, DIAM_X
    - SendAll(): полное состояние при READY/PONG от ESP32
    - RX парсер: <TOUCH:*>, <READY>, <PONG> → DispRxCmd_t
2026-04-06 feat(etap4): драйвер LCD2004 — I2C1/PCF8574 HD44780 4-bit протокол
2026-04-06 feat(etap5): GPIO входы — джойстик, кнопки меню, лимиты, переключатели режима, дебаунс 12мс
2026-04-06 feat(etap6): энкодеры — TIM5 квадратурный счётчик шпинделя (×4, RPM), EXTI ручной энкодер
2026-04-06 feat(etap7): шаговые двигатели — TIM1 HardwareTimer PWM, STEP/DIR/EN, позиция в ISR callback
2026-04-06 feat(etap8-9): замкнутый контур ELS (FEED/AFEED/THREAD/CONE) + Serial Monitor команды
2026-04-06 feat(etap10): README.md + симулятор DRO HS800-2 (Arduino sketch, 4 режима)
2026-04-13 feat(etap10-14): физ. кнопки, меню, таблицы резьб/конусов, Serial Monitor, fix LCD white screen
    Этап 10-11: физические кнопки и меню
    - els_menu.cpp/h: ELS_Menu_Process() — ротарный переключатель режимов M1-M8
    (PG8-PG15), переключатель подрежимов (PG5-PG7), навигация UP/DOWN/SELECT с авто-повтором
    - Смена режима: сброс Ap=0, Pass_Nr=1, select_menu=1, ELS_Control_Stop()
    - _key_up/_key_down: редактирование Thread_Step, Cone_Step, Ap, Ph, Sph_R_mm, Total_Tooth
    Этап 12: таблицы резьб и конусов
2026-04-13 fix(display): приоритетная отправка MODE/SUBMODE/SELECTMENU на ESP32
    DRV_Display_SendCmd() дропал команды если TX буфер занят (< 32 байт).
    При высокочастотных POS обновлениях буфер мог быть занят в момент
    ответа на touch команду → ESP32 не получал MODE/SUBMODE → режим
    не переключался на новом дисплее хотя на LCD2004 уже был новый.
    Добавлена _SendCmdPriority() — ждёт освобождения буфера до 10мс.
    Используется для MODE, SUBMODE, SELECTMENU.
2026-04-13 Fix: TOUCH_PARAM_OK обработка + интервал 250мс для ESP32
    - els_menu.cpp: добавлен case TOUCH_PARAM_OK → _key_select()
    Двойной тач row6 теперь переключает select_menu (саб-режим).
    Ранее команда игнорировалась → подрежим никогда не менялся.
    - els_main.cpp: интервал отправки позиций/RPM на ESP32 100→250мс
    (совпадает с оригинальным Arduino, снижает нагрузку на ESP32)
2026-04-14 fix: отправлять AP:0 на ESP32 при смене режима через переключатель
    _switch_mode_hw сбрасывал els.Ap=0 но не уведомлял ESP32.
    Стало: DRV_Display_SendInt("AP", 0) после смены режима —
    устраняет мигание Съёма в row3 (режимы 1-2) и row5 (Конус).
2026-04-14 fix: _set_mode (touch) теперь тоже сбрасывает Ap=0 и шлёт AP:0
2026-05-01 fix(display): roller резьбы открывается на правильной позиции после смены типа
    jump_to_thread_type: local_step устанавливается ДО enter_edit_mode(),
    чтобы roller открылся на первой записи выбранного типа, а не на старой.
2026-05-01 feat(BACKLOG-001): GCode WiFi веб-интерфейс — фаза 1 (файловый менеджер)
    - gcode_wifi.cpp/h: неблокирующий WiFi (STA → AP fallback), LittleFS /gcode,
    AsyncWebServer порт 80, REST API (/api/status, /api/files, /api/upload,
    /api/file GET/DELETE, /api/wifi), HTML веб-UI в PROGMEM
    - Удалён хардкод WiFi из main.cpp; GCodeWiFi_Init/Process интегрированы
    - Скриншот-сервер перенесён с порта 80 на 8081
    - partitions_8mb.csv: 4MB app + 4MB LittleFS для 8MB flash JC4827W543
2026-05-01 feat(BACKLOG-001): WiFi настройки через wifi_config.h + IP в меню настроек
    - wifi_config.h: пользователь задаёт WIFI_STA_SSID/PASS для роутера,
    или оставляет пустым → ESP32 поднимает AP "ELS-WiFi" / "12345678"
    - gcode_wifi: убраны Preferences для WiFi, только compile-time defines;
    добавлен GCodeWiFi_SetConnectedCallback для уведомления об IP
    - settings_menu: секция WIFI показывает режим (STA/AP) и IP адрес;
    обновляется каждые 5 сек из loop()
2026-05-01 fix(display): GCodeWiFi_Init после create_dark_pro_ui — убрать чёрный экран
    LittleFS.begin(formatOnFail) и WiFi.softAP вызывались до LVGL init и
    create_dark_pro_ui(), поэтому экран оставался чёрным на время инициализации.
    Переставлено: сначала UI отрисовывается (lv_timer_handler), потом WiFi/LittleFS.
2026-05-02 fix(display): httpd_start перенесён после GCodeWiFi_Init — убрать крах lwIP
    httpd_start() вызывался до инициализации WiFi стека (до GCodeWiFi_Init),
    что приводило к краху lwIP socket() и чёрному экрану. Теперь httpd
    запускается строго после GCodeWiFi_Init() когда стек готов.
